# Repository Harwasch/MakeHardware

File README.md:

# MakeHardware

A Claude Code **plugin** that teaches AI agents to do hardware engineering, and
the cloud environment that gives them the tools to do it.

This repo is not a hardware project. It holds the workflow, practices, skills
and definitions; the projects themselves live in their own repos and install
this plugin.

```
MakeHardware  (this repo)          your-widget  (a project repo)
├── the workflow                   ├── plan.yaml
├── the skills                 ──► ├── requirements/
├── the house practices            ├── cad/  hw/  sim/
└── the environment setup          └── docs/{reference,design,user}
```

## Using it on a project

**Start here: [docs/03-using-it.md](docs/03-using-it.md)** walks through a whole
project from a one-sentence idea to a verified design.

The short version — in the project repo's `.claude/settings.json`:

```json
{
  "extraKnownMarketplaces": {
    "makehardware": {
      "source": { "source": "github", "repo": "Harwasch/MakeHardware" }
    }
  },
  "enabledPlugins": { "makehardware@makehardware": true }
}
```

That is enough on a local machine you have trusted for plugins. **In a cloud
session it is not sufficient on its own** — a repo-declared marketplace is
ignored for an untrusted folder, and `enabledPlugins` never installs anything.
The environment's setup script therefore installs the plugin at user scope; see
[docs/01-environment.md](docs/01-environment.md#why-the-setup-script-installs-the-plugin).

Then point the project at a cloud environment built from [`env/`](env/) and run
`/hw-new-project` to scaffold it.

To stop copying that file into every new repo by hand, make a **GitHub template
repository** out of [`templates/github-repo/`](templates/github-repo) — see
[docs/04-template-repo.md](docs/04-template-repo.md).

## The workflow

```
1 VISION ─► 2 PLAN ─► 3 REQS ─► 4 ARCHITECTURE ─► 5 DESIGN ─► 6 SIMULATE ─► 7 VERIFY
 interview   chunks &  decompose  block diagram    schematic   ngspice       evidence
 + renders   deps      + validate  + power budget   + CAD       FEA           + gate
     ▲          ▲          ▲            ▲              ▲           │            │
     │          │          │            │              └───────────┘            │
     │          │          │            └──── a rail is short ──────┤            │
     │          │          └────────── numbers must move ───────────┤            │
     └──────────┴──────── the thing is not what they meant ─────────────────────┘
```

Stages 1–4 are agreements with a human. Stages 5–7 are a loop. Full detail in
[docs/02-workflow.md](docs/02-workflow.md).

**Every agreement is a recorded one.** The agent is normally working in a cloud
VM, so the human's only review surface is this repository on github.com. At each
milestone the agent commits an artefact that renders there — a vision document,
the plan's scope and Gantt, the requirements map, the block diagram, a schematic
PDF — asks the human directly with the link, and records what they said in
`docs/review/reviews.yaml`. `review-gate check --gate` fails while a milestone
is unanswered, or while an artefact has changed since it was signed off. A
chunk in `plan.yaml` cannot be marked `done` until its review is signed and its
declared outputs exist on disk.

Alongside the repo there is **one review page per project** — `review-artifact`
builds `docs/review/artifact.html` from the repo and it is published as a
Claude Artifact: a tab per phase, every figure and number read from the file
that owns it, and the human comments on it in place. GitHub is the record; the
page is the thing they actually read. `review-artifact --init` writes its
config, and `--url` records where it was published so every later session
updates that page rather than making a second one.

The rule behind it: **an artefact the human has not seen is not a deliverable.**
And its corollary, which is what most of 0.4.0 is about: an artefact they
cannot *read* has not been seen. A schematic nobody can follow, a STEP file
that opens as one unnamed solid, and a wall of numbers where a chart belongs
are all deliverables in name only.

## What the plugin provides

| | |
|---|---|
| **Skills** | `hw-vision`, `hw-planning`, `hw-requirements`, `hw-block-diagram`, `hw-schematic`, `hw-pcb-layout`, `hw-cad`, `hw-optimize`, `hw-review`, `hw-visuals`, `hw-sourcing`, `hw-simulation`, `hw-magnetics`, `hw-verification`, `hw-documentation`, `hw-imagegen`, `hw-retro` |
| **Commands** | `/hw-new-project`, `/hw-status`, `/hw-review`, `/hw-retro` |
| **Gates** | `sch-lint`, `pcb-lint`, `cad-export --check`, `req-trace --gate`, `block-diagram --check`, `plan-render --check`, `review-gate check`, `hw-iterate status --gate` |
| **Tools on PATH** | `hw-doctor`, `hw-repair`, `plan-render`, `req-trace`, `block-diagram`, `vision-board`, `review-gate`, `review-artifact`, `sch-lint`, `pcb-lint`, `cad-export`, `hw-chart`, `hw-iterate`, `hw-feedback`, `imagegen` |
| **MCP servers** | `spice` (ngspice/LTspice), `build123d` |
| **Templates** | An A3 KiCad drawing sheet and the house grid, text sizes and net classes |
| **Practices** | House standards for schematic and board drawing, sourcing, connectors, passives and charts — edited over time to steer the agent |

## The toolchain

| Layer | Tool |
|---|---|
| Human review | `review-gate` — artefacts that render on GitHub, a link put to the human, a committed sign-off with a digest per artefact |
| Requirements | StrictDoc, with a hardware grammar and a traceability gate, plus a draw.io/SVG requirements map |
| Architecture | `block-diagram` — one YAML spec renders an editable draw.io file, a review SVG, and a power budget with a gate |
| Planning | `plan-render` — a dependency Gantt, an editable draw.io graph, and a scope document, with `done` checked against the filesystem |
| Schematic / PCB | KiCad 10 + [KiStack](https://github.com/American-Embedded/KiStack) skills over `kicad-cli` and `kicad-python` |
| Circuit simulation | ngspice via `ltspice-mcp`; LTspice opt-in |
| 3D CAD | build123d + `build123d-mcp` |
| Meshing / FEA | gmsh + CalculiX |
| Vision imagery | build123d renders for geometry; HF Spaces or a keyed API for styling |
| Design review | [kicad-happy](https://github.com/aklofas/kicad-happy) — EMC, thermal, derating, distributor search |

Why each, and what was rejected: [docs/00-stack.md](docs/00-stack.md).

## Setting up the environment

Three fields in the cloud environment dialog at
[claude.ai/code](https://claude.ai/code):

1. **Network access → Full.** Nothing to paste. Sourcing and documentation
   mean fetching datasheets from vendors you can't enumerate in advance, so an
   allowlist makes every new manufacturer a config change.
   [`env/allowed-domains.txt`](env/allowed-domains.txt) has the tighter
   Custom fallback if you'd rather not run open — note that on **Trusted** you
   silently get KiCad 7 instead of 10.
2. **Environment variables** ← [`env/environment-variables.env`](env/environment-variables.env)
3. **Setup script** ← [`env/setup.sh`](env/setup.sh) — this also installs the
   plugin itself, which is why a cloud session gets the skills and MCP servers
   without a trust dialog.

Then run `hw-doctor` in a session. Details and the five failure modes the
script works around: [docs/01-environment.md](docs/01-environment.md).

## Layout

```
.claude-plugin/marketplace.json   marketplace manifest
plugins/makehardware/
├── skills/                       the workflow stages
├── commands/                     /hw-new-project, /hw-status, /hw-review, /hw-retro
├── bin/                          hw-doctor, hw-repair, plan-render, req-trace,
│                                 block-diagram, vision-board, review-gate,
│                                 review-artifact, hw-chart, hw-iterate, imagegen
├── scripts/                      their implementations
└── .mcp.json                     spice, build123d
templates/github-repo/            contents of the GitHub template repository
examples/thermal-probe/           a worked project, part-way through — see below
env/                              cloud environment configuration
docs/                             stack rationale, environment, workflow
tests/smoke.sh                    scaffolds a throwaway project and drives the gates
tests/real-tool-output.sh         what the review page does with real exporter output
tests/version-bump.sh             refuses a plugin change that did not bump the version
CHANGELOG.md                      what changed, per version
CLAUDE.md                         house rules for working on this repo
```

`tests/smoke.sh` needs only `python3` with `pyyaml`. It scaffolds a project
from the template and checks the things that used to have nothing behind them:
a `done` chunk whose outputs are missing, a `done` chunk whose review is
unsigned, an artefact edited after sign-off, and the power budget's voltage
referral.

`tests/real-tool-output.sh` covers the other half: what the review page does
when it is handed what the real tools emit rather than what we would write by
hand. Page size in millimetres, a `<style>` block whose selectors are global
once inlined, KiCad 10's layer-named ids colliding between sheets, a
megabyte-and-a-half render, a PDF, and an export that silently did not happen.

## Releasing

Any change under `plugins/makehardware/` must bump the version in **both**
`.claude-plugin/marketplace.json` and
`plugins/makehardware/.claude-plugin/plugin.json`, with a `CHANGELOG.md` entry
in the same commit.

This is not housekeeping. `claude plugin install` treats an already-installed
plugin at the same version as nothing to do, so a version that does not move
means a user who runs `claude plugin marketplace update makehardware` fetches
the new source, sees a version they already have and **keeps running the old
code**. `tests/version-bump.sh` fails the build when it happens.

Users on an existing cloud environment pick up a release either by rebuilding
the environment — `env/setup.sh` installs the plugin at container build — or
with `claude plugin marketplace update makehardware` in a live session.

## The worked example

[`examples/thermal-probe/`](examples/thermal-probe) is a project caught
part-way through: one milestone approved, one awaiting an answer, one gone
stale because an artefact moved underneath it, and one never requested. It is
what the review page is developed against.

```bash
cd examples/thermal-probe && ./build-fixture.sh
```

rebuilds every artefact from its spec — including the schematic sheets, which
are genuine `kicad-cli sch export svg` output where `kicad-cli` is installed,
because what a plotter emits is nothing like what you would draw by hand.

## Docs

* [docs/00-stack.md](docs/00-stack.md) — choices, rejections, measured build budget
* [docs/01-environment.md](docs/01-environment.md) — environment configuration
* [docs/02-workflow.md](docs/02-workflow.md) — the seven stages and their exit conditions
* [docs/03-using-it.md](docs/03-using-it.md) — how you actually run a project with it
* [docs/04-template-repo.md](docs/04-template-repo.md) — a GitHub template repo so new projects start correct

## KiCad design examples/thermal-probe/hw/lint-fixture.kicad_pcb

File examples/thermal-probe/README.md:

# Thermal Probe

Example project used to develop the MakeHardware review artifact.

<!-- PLAN:BEGIN -->
<!-- generated by plan_render.py — edit plan.yaml, not this block -->

**0/11 chunks complete** · 10 sessions on the critical path · [editable version](docs/plan.drawio)

<!-- PLAN:END -->

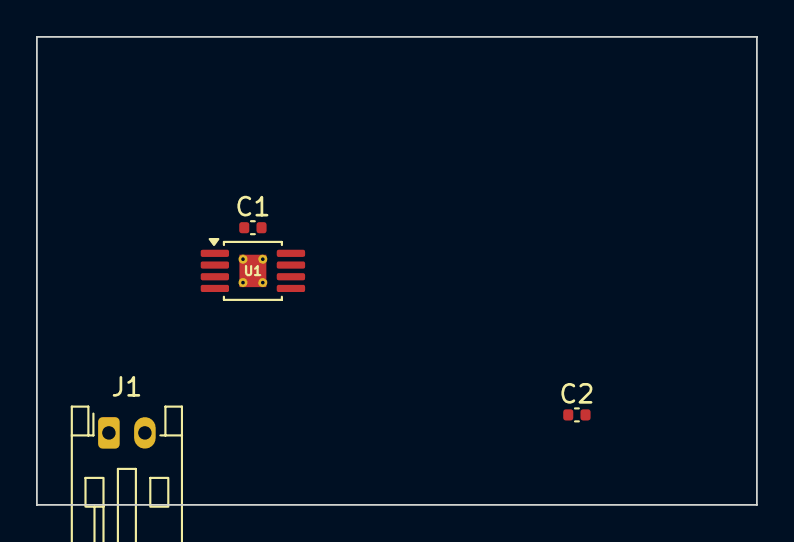
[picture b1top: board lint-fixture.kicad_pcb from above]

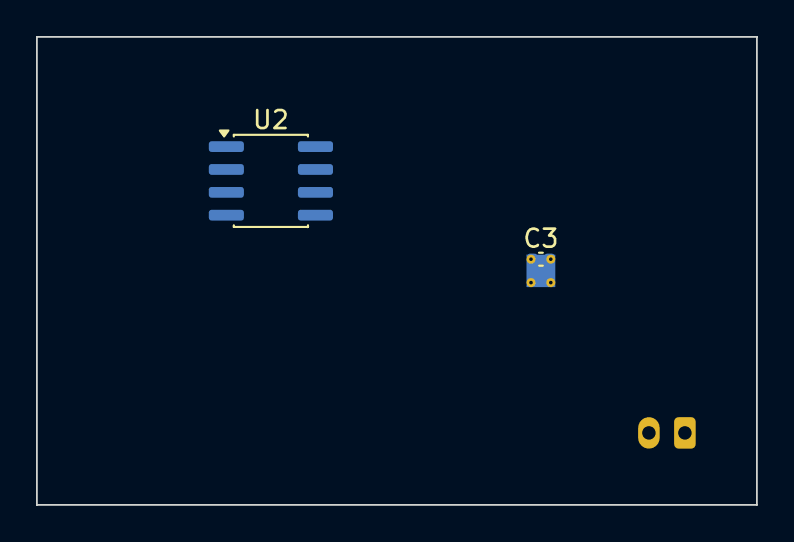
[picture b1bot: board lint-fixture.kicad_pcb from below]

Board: 2 copper layers, 40.0 x 26.0 mm, 6 parts (2 on the bottom side), 4 nets, no tracks yet.

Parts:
C1, C2: 100nF; C_0402_1005Metric
C3: 1uF; C_0402_1005Metric
J1: VIN; JST_PH_S2B-PH-K_1x02_P2.00mm_Horizontal
U1: TPS62840; MSOP-8-1EP_3x3mm_P0.65mm_EP1.5x1.8mm_ThermalVias
U2: OPA377; SOIC-8_3.9x4.9mm_P1.27mm

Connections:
GND: C1.2, C2.2, J1.2, U1.2, U1.9, U2.4
SENSE: C3.1, U2.1, U2.7
SW_NODE: C3.2, U1.1
VDD: C1.1, C2.1, J1.1, U1.5, U1.8, U2.8
